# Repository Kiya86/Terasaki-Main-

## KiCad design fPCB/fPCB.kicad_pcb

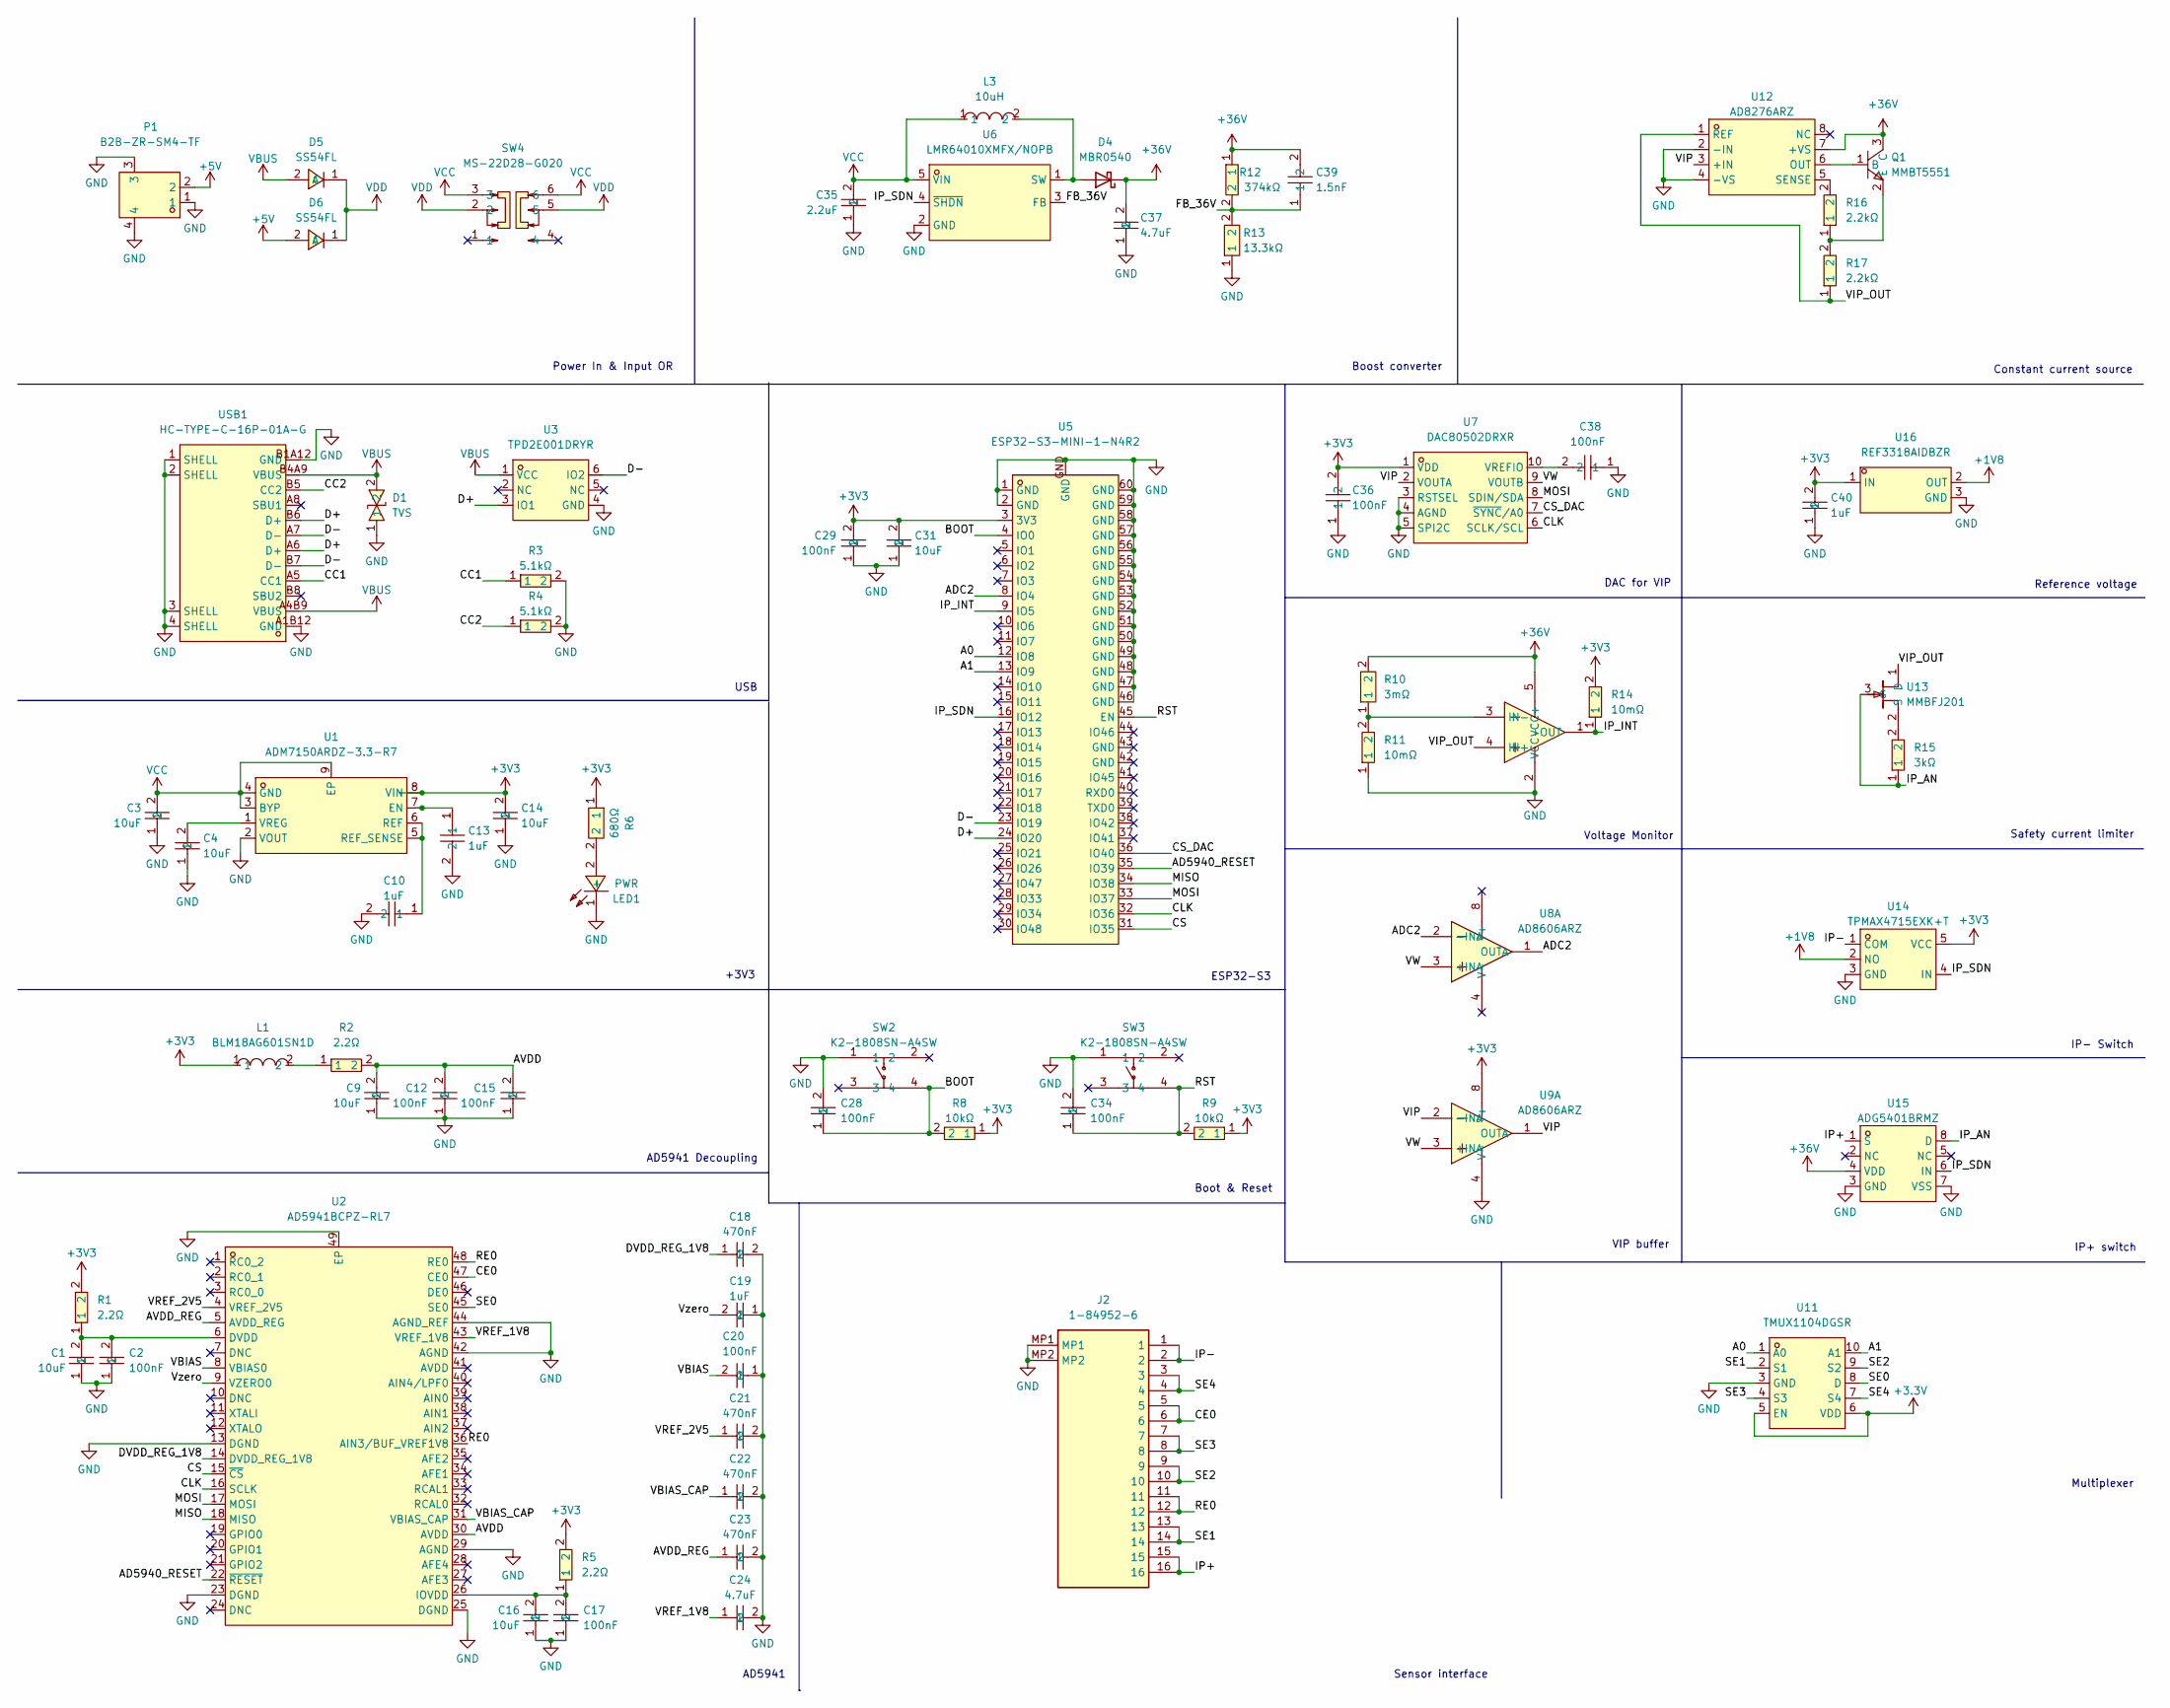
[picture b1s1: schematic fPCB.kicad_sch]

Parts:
C1, C9, C16, C31: 10uF; C0805; MPN CL21A106KOQNNNE; LCSC Part C1713
C2, C12, C15, C17, C20, C28, C29, C34: 100nF; C0603; MPN GRM188R71C104KA01D; LCSC Part C45000
C3, C4, C14: 10uF; C0805; MPN CL21B106KPQNNNE; LCSC Part C32635
C10, C13: 1uF; C0603; MPN CL10B105KP8NNNC; LCSC Part C95843
C18, C21, C22, C23: 470nF; C0402; MPN CC0402KRX5R6BB474; LCSC Part C106255
C19: 1uF; C0603; MPN CL10A105KO8NNNC; LCSC Part C1592
C24, C37: 4.7uF; C0603; MPN CL10A475KP8NNNC; LCSC Part C1705
C35: 2.2uF; C0603; MPN CL10A225KO8NNNC; LCSC Part C23630
C36, C38: 100nF; C0603; MPN GRM188R71H104KA93D; LCSC Part C77055
C39: 1.5nF; C0402; MPN GRM1555C1H152JA01D; LCSC Part C668348
C40: 1uF; C0402; MPN CL05A105KP5NNNC; LCSC Part C14445
D1: TVS; SOD-523_L1.2-W0.8-LS1.6-BI; MPN LESD5D5.0CT1G; LCSC Part C383211
D4: MBR0540; D_SOD-123
D5, D6: SS54FL; SMAF_L3.5-W2.6-LS4.7-RD; MPN SS54FL; LCSC Part C115939
J2: 1-84952-6; 1849526; Mouser Part Number 571-1-84952-6
L1: BLM18AG601SN1D; L0603; MPN BLM18AG601SN1D; LCSC Part C19330
L3: 10uH; L0603; MPN MLZ1608M100WT000; LCSC Part C76798
LED1: PWR; LED0805-RD; MPN NCD0805R1; LCSC Part C84256
P1: B2B-ZR-SM4-TF; CONN-SMD_B2B-ZR-SM4-TF-LF-SN; MPN B2B-ZR-SM4-TF(LF)(SN); LCSC Part C265284
Q1: MMBT5551; SOT-23-3_L2.9-W1.3-P1.90-LS2.4-BR; MPN MMBT5551; LCSC Part C916370
R1, R2, R5: 2.2Ω; R0402; MPN RC0402FR-072R2L; LCSC Part C327251
R3, R4: 5.1kΩ; R0402; MPN 0402WGF5101TCE; LCSC Part C25905
R6: 680Ω; R0402; MPN ERJ2RKF6800X; LCSC Part C413078
R8, R9: 10kΩ; R0603; MPN 0603WAJ0103T5E; LCSC Part C15401
R10: 3mΩ; R0603; MPN FRC0603J305 TS; LCSC Part C2907163
R11, R14: 10mΩ; R0603; MPN RC0603FR-0710ML; LCSC Part C114606
R12: 374kΩ; R0402; MPN 0402WGF3743TCE; LCSC Part C25781
R13: 13.3kΩ; R0402; MPN FRC0402F1332TS; LCSC Part C2974007
R15: 3kΩ; R0402; MPN RC0402FR-073KL; LCSC Part C137987
R16, R17: 2.2kΩ; R0603; MPN RC0603FR-072K2L; LCSC Part C114662
SW2, SW3: K2-1808SN-A4SW; KEY-SMD_4P-L4.2-W3.2-P2.20-LS5.1-TL; MPN K2-1808SN-A4SW-01; LCSC Part C92589
SW4: MS-22D28-G020; SW-SMD_MS-22D28-G020; MPN MS-22D28-G020; LCSC Part C963205
U1: ADM7150ARDZ-3.3-R7; SOIC-8_L4.9-W3.9-P1.27-LS6.0-BL-EP3.1; MPN ADM7150ARDZ-3.3-R7; LCSC Part C658444
U2: AD5941BCPZ-RL7; LFCSP-48_L7.0-W7.0-P0.50-BL-EP5.1; MPN AD5941BCPZ-RL7; LCSC Part C650309
U3: TPD2E001DRYR; SON-6_L1.5-W1.0-P0.50-BL; MPN TPD2E001DRYR; LCSC Part C379992
U5: ESP32-S3-MINI-1-N4R2; BULETM-SMD_ESP32-S3-MINI-1-N8; MPN ESP32-S3-MINI-1-N4R2; LCSC Part C3013941
U6: LMR64010XMFX/NOPB; SOT-23-5_L3.0-W1.7-P0.95-LS2.8-BR; MPN LMR64010XMFX/NOPB; LCSC Part C165138
U7: DAC80502DRXR; WSON-10_L2.5-W2.5-W0.50-BL; MPN DAC80502DRXR; LCSC Part C1880990
U8, U9: AD8606ARZ; SOIC-8_L4.9-W3.9-P1.27-LS6.0-BL; MPN AD8606ARZ; LCSC Part C578773
U10: TS391ILT; SOT-23-5_L3.0-W1.7-P0.95-LS2.8-BR; MPN TS391ILT; LCSC Part C71896
U11: TMUX1104DGSR; VSSOP-10_L3.0-W3.0-P0.50-LS4.9-BL; MPN TMUX1104DGSR; LCSC Part C2879206
U12: AD8276ARZ; SOIC-8_L4.9-W3.9-P1.27-LS6.0-BL; MPN AD8276ARZ; LCSC Part C652621
U13: MMBFJ201; SOT-23-3_L2.9-W1.3-P1.90-LS2.4-BR; MPN MMBFJ201; LCSC Part C891687
U14: TPMAX4715EXK+T; SOT-353_L2.2-W1.4-P0.65-LS2.4-BR; MPN TPMAX4715EXK+T; LCSC Part C46472308
U15: ADG5401BRMZ; MSOP-8_L3.0-W3.0-P0.65-LS4.9-BL; MPN ADG5401BRMZ; LCSC Part C657485
U16: REF3318AIDBZR; SOT-23-3_L3.0-W1.7-P0.95-LS2.9-BR; MPN REF3318AIDBZR; LCSC Part C115877
USB1: HC-TYPE-C-16P-01A-G; USB-C-SMD_G-SWITCH_GT-USB-7010EN; MPN HC-TYPE-C-16P-01A-G; LCSC Part C2997435

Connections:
+1V8: U14.2 (NO), U16.2 (OUT)
+3.3V: U11.5 (EN), U11.6 (VDD)
+3V3: C14.2, C29.2, C31.2, C36.2, C40.2, L1.1, R1.2, R5.2, R6.1, R8.1, R9.1, R14.2, U1.8 (VIN), U5.3 (3V3), U7.1 (VDD), U9.8 (V+), U14.5 (VCC), U16.1 (IN)
+5V: D6.2 (A), P1.2
+36V: C37.2, C39.2, D4.1 (K), Q1.3 (C), R10.2, R12.1, U10.5 (VCC+), U12.7 (+VS), U15.4 (VDD)
/A0: U5.12 (IO8), U11.1 (A0)
/A1: U5.13 (IO9), U11.10 (A1)
/AD5940_RESET: U2.22 (~RESET), U5.35 (IO39)
/ADC2: U5.8 (IO4), U8.1 (OUTA), U8.2 (-INA)
/AVDD: C9.2, C12.2, C15.2, R2.2, U2.30 (AVDD)
/AVDD_REG: C23.1, U2.5 (AVDD_REG)
/BOOT: C28.1, R8.2, SW2.4, U5.4 (IO0)
/CC1: R3.1, USB1.A5 (CC1)
/CC2: R4.1, USB1.B5 (CC2)
/CE0: J2.5, J2.6, U2.47 (CE0)
/CLK: U2.16 (SCLK), U5.32 (IO36), U7.6 (SCLK/SCL)
/CS: U2.15 (~CS), U5.31 (IO35)
/CS_DAC: U5.36 (IO40), U7.7 (~SYNC/A0)
/D+: U3.3 (IO1), U5.24 (IO20), USB1.A6 (D+), USB1.B6 (D+)
/D-: U3.6 (IO2), U5.23 (IO19), USB1.A7 (D-), USB1.B7 (D-)
/DVDD_REG_1V8: C18.1, U2.14 (DVDD_REG_1V8)
/FB_36V: C39.1, R12.2, R13.2, U6.3 (FB)
/IP+: J2.15, J2.16, U15.1 (S)
/IP-: J2.1, J2.2, U14.1 (COM)
/IP_AN: R15.1, U13.3 (G), U15.8 (D)
/IP_INT: R14.1, U5.9 (IO5), U10.1 (OUT)
/IP_SDN: U5.16 (IO12), U6.4 (~SHDN), U14.4 (IN), U15.6 (IN)
/MISO: U2.18 (MISO), U5.34 (IO38)
/MOSI: U2.17 (MOSI), U5.33 (IO37), U7.8 (SDIN/SDA)
/RE0: J2.11, J2.12, U2.36 (AIN3/BUF_VREF1V8), U2.48 (RE0)
/RST: C34.1, R9.2, SW3.4, U5.45 (EN)
/SE0: U2.45 (SE0), U11.8 (D)
/SE1: J2.13, J2.14, U11.2 (S1)
/SE2: J2.9, J2.10, U11.9 (S2)
/SE3: J2.7, J2.8, U11.4 (S3)
/SE4: J2.3, J2.4, U11.7 (S4)
/VBIAS: C20.2, U2.8 (VBIAS0)
/VBIAS_CAP: C22.1, U2.31 (VBIAS_CAP)
/VIP: U7.2 (VOUTA), U9.1 (OUTA), U9.2 (-INA), U12.3 (+IN)
/VIP_OUT: R17.1, U10.4 (IN+), U12.1 (REF), U13.1 (D)
/VREF_1V8: C24.1, U2.43 (VREF_1V8)
/VREF_2V5: C21.1, U2.4 (VREF_2V5)
/VW: U7.9 (VOUTB), U8.3 (+INA), U9.3 (+INA)
/Vzero: C19.2, U2.9 (VZERO0)
GND: C1.1, C2.1, C3.1, C4.1, C9.1, C10.2, C12.1, C13.2, C14.1, C15.1, C16.1, C17.1, C18.2, C19.1, C20.1, C21.2, C22.2, C23.2, C24.2, C28.2, C29.1, C31.1, C34.2, C35.1, C36.1, C37.1, C38.1, C40.1, D1.1, J2.MP1, J2.MP2, LED1.1 (-), P1.1, P1.3, P1.4, R3.2, R4.2, R11.1, R13.1, SW2.1, SW3.1, U1.2 (VOUT), U2.13 (DGND), U2.23 (DGND), U2.25 (DGND), U2.29 (AGND), U2.42 (AGND), U2.44 (AGND_REF), U2.49 (EP), U3.4 (GND), U5.1 (GND), U5.2 (GND), U5.46 (GND), U5.47 (GND), U5.48 (GND), U5.49 (GND), U5.50 (GND), U5.51 (GND), U5.52 (GND), U5.53 (GND), U5.54 (GND), U5.55 (GND), U5.56 (GND), U5.57 (GND), U5.58 (GND), U5.59 (GND), U5.60 (GND), U5.GND, U6.2 (GND), U7.3 (RSTSEL), U7.4 (AGND), U7.5 (SPI2C), U9.4 (V-), U10.2 (VCC-), U11.3 (GND), U12.2 (-IN), U12.4 (-VS), U14.3 (GND), U15.3 (GND), U15.7 (VSS), U16.3 (GND), USB1.1 (SHELL), USB1.2 (SHELL), USB1.3 (SHELL), USB1.4 (SHELL), USB1.A1B12 (GND), USB1.B1A12 (GND)
unnamed: D4.2 (A), L3.2, U6.1 (SW)
unnamed: L1.2, R2.1
unnamed: LED1.2 (+), R6.2
unnamed: Q1.1 (B), U12.6 (OUT)
unnamed: Q1.2 (E), R16.1, R17.2
unnamed: C13.1, U1.7 (EN)
unnamed: C10.1, U1.5 (REF_SENSE), U1.6 (REF)
unnamed: C4.2, U1.1 (VREG)
unnamed: C1.2, C2.2, R1.1, U2.6 (DVDD)
unnamed: C16.2, C17.2, R5.1, U2.26 (IOVDD)
unnamed: C38.2, U7.10 (VREFIO)
unnamed: R10.1, R11.2, U10.3 (IN-)
unnamed: R16.2, U12.5 (SENSE)
unnamed: R15.2, U13.2 (S)
VBUS: D1.2, D5.2 (A), U3.1 (VCC), USB1.A4B9 (VBUS), USB1.B4A9 (VBUS)
VCC: C3.2, C35.2, L3.1, SW4.3, SW4.6, U1.3 (BYP), U1.4 (GND), U1.9 (EP), U6.5 (VIN)
VDD: D5.1 (C), D6.1 (C), SW4.2, SW4.5

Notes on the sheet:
USB
Reference voltage
Voltage Monitor
AD5941 Decoupling
ESP32-S3
AD5941
Constant current source
+3V3
IP- Switch
Power In & Input OR
IP+ switch
Boot & Reset
DAC for VIP
Sensor interface
Safety current limiter
Multiplexer
VIP buffer
Boost converter

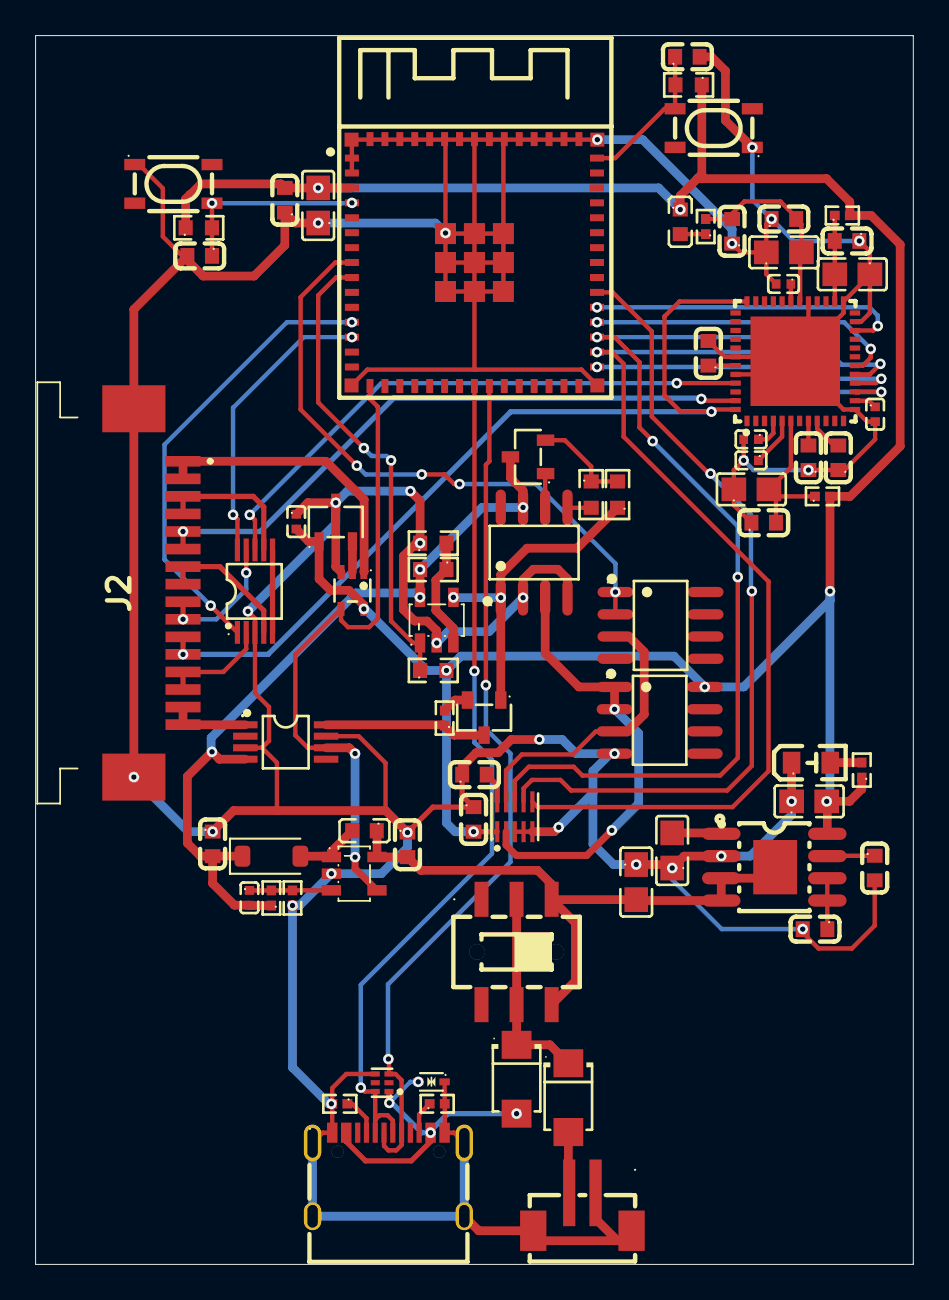
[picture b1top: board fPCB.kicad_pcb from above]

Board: 2 copper layers, 50.0 x 70.0 mm, 74 parts (0 on the bottom side), 62 nets.

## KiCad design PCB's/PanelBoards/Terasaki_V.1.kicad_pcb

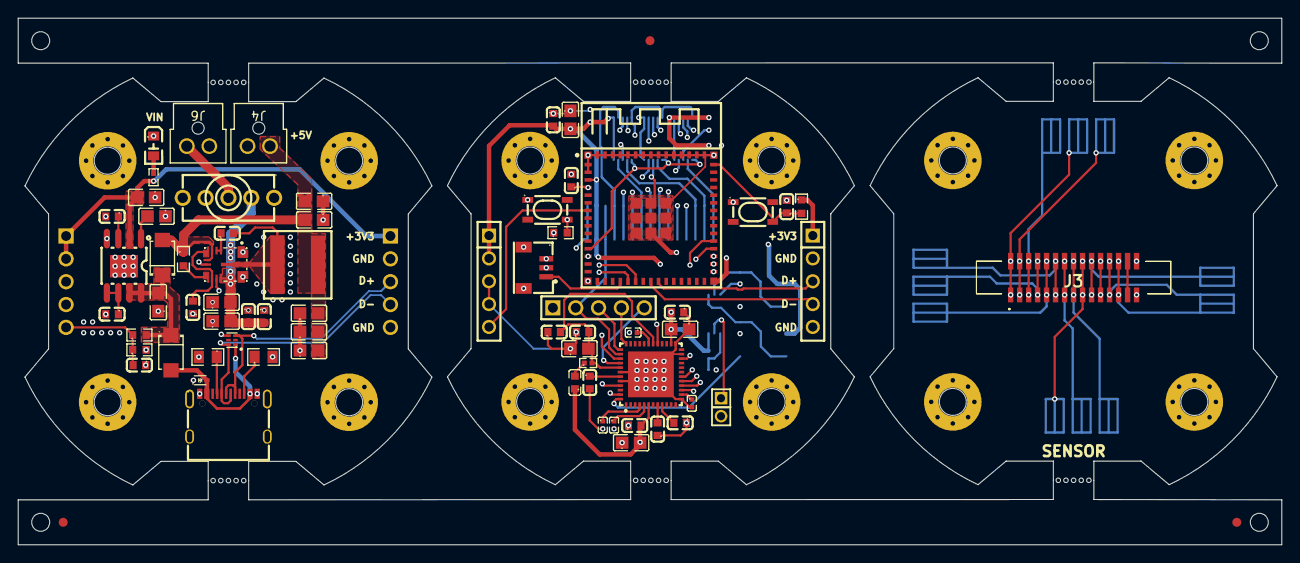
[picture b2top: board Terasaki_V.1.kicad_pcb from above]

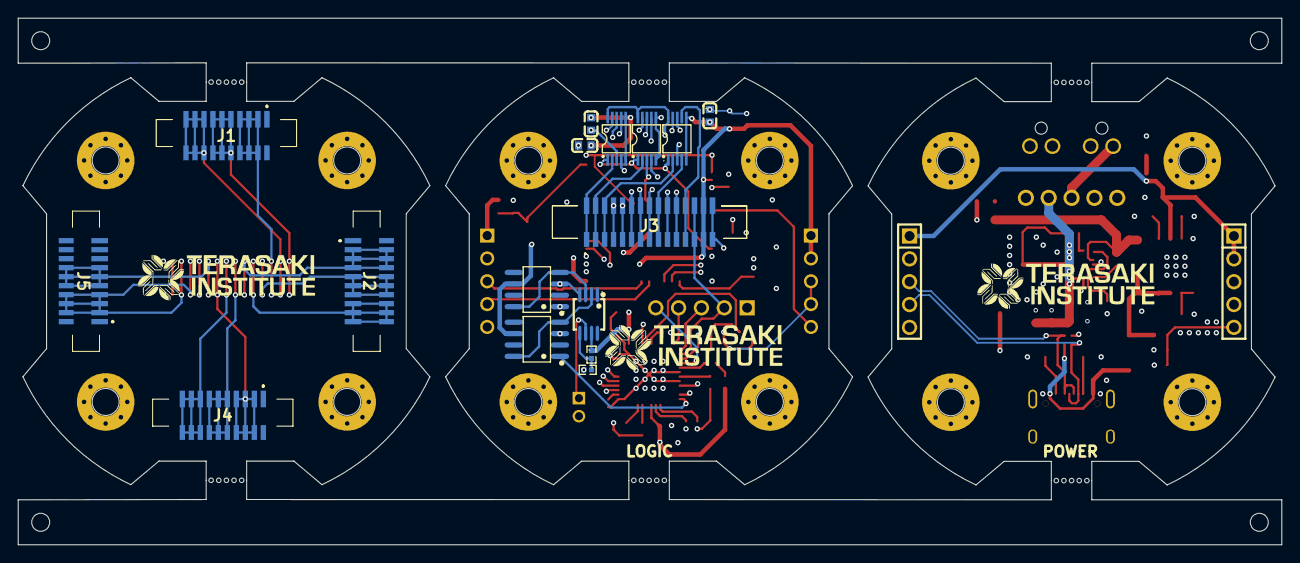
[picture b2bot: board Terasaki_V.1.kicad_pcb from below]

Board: 4 copper layers, 140.5 x 58.5 mm, 85 parts (18 on the bottom side), 65 nets.

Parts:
C1, C2, C3, C12, C16, C21, C27, C28, C34, C35, C36#2, C37#2, C38: 100nF; C0603
C5, C10, C37, C39: 1uF; C0603
C6, C11, C17, C18, C20, C22, C24, C26, C36: 10uF; C0805
C9, C25: 470nF; C0603
C13, C14, C15, C19, C23: 22uF; C0805
C29: 4.7uF; C0603
C30, C31, C32, C33: 470nF; C0402
D1: TVS; SOD-523_L1.2-W0.8-LS1.6-BI
D2, D3: SS54FL; SMAF_L3.5-W2.6-LS4.7-RD
H1: MTP220-1102S1; HDR-TH_2P-P2.00-V-M
H2, H3#2: A2541WV-5P; HDR-TH_5P-P2.54-V-M
H3, H4: Header-Female; HDR-TH_5P-P2.54-V-F
H5: Header; HDR-TH_5P-P2.54-H-M-W7.7-P
J1, J2, J4#2, J5: 1-1734248-0; 117342480
J3, J3#2: 52610-1572; 526101572
J4, J6: 1053091202; CONN_SD-105309-100_02_MOL
L1: 2.7uH; IND-SMD_L7.5-W7.5_XAL7030
L2: BLM18AG601SN1D; L0603
LED1: FC-2012HRK-620D; LED0805-RD
R1, R2, R9: 10kΩ; R0603
R3, R4: 5.5kΩ; R0805
R6, R10: 100kΩ; R0603
R7: 2.2Ω; R0402
R8: 680Ω; R0402
R12, R13: 100kΩ; R0402
SW1: 2MS1T2B2VS2QES; SW-TH_2MS1T2B2VS2QES
SW1#2, SW2: K2-1808SN-A4SW; KEY-SMD_4P-L4.2-W3.2-P2.20-LS5.1-TL
U1: ESP32-S3-MINI-1-N4R2; BULETM-SMD_ESP32-S3-MINI-1-N8
U2: INA333AIDGKR; MSOP-8_L3.0-W3.0-P0.65-LS5.0-BL
U3: TPD2E001DRYR; SON-6_L1.5-W1.0-P0.50-BL
U3#2, U5#2, U9#2: TMUX1104DGSR; VSSOP-10_L3.0-W3.0-P0.50-LS4.9-BL
U4: AD5941BCPZ-RL7; LFCSP-48_L7.0-W7.0-P0.50-BL-EP5.1
U5: ADM7150ARDZ-3.3-R7; SOIC-8_L4.9-W3.9-P1.27-LS6.0-BL-EP3.1
U6: BM03B-SRSS-TB; CONN-SMD-3P-P1.00_BM03B-SRSS-TB-LF-SN
U9: LM61495Q5RPHRQ1_C3188409; VQFN-16_L4.5-W3.5-P0.50-TL_TI_RPH
U11, U14: LMP7721MA/NOPB; SOIC-8_L4.9-W3.9-P1.27-LS6.0-BL
USB1: HC-TYPE-C-16P-01A-G; USB-C-SMD_G-SWITCH_GT-USB-7010EN

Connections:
+3V3: C1.2, C6.2, C17.2, C20.2, C21.2, C22.2, C35.2, C36#2.2, C37#2.2, C38.2, H2.1, H2.2, H3.1, H3.2, H3#2.1, H4.1, J3.27, J3.28, J3#2.27, J3#2.28, L2.1, R1.1, R2.1, R8.1, R12.1, U1.3 (3V3), U2.7 (V+), U3#2.5 (EN), U3#2.6 (VDD), U4.6 (DVDD), U4.26 (IOVDD), U5.2 (VOUT), U5#2.5 (EN), U5#2.6 (VDD), U9#2.5 (EN), U9#2.6 (VDD), U11.6 (V+), U14.6 (V+)
+5V: C13.2, C14.2, C15.2, C19.2, C23.2, D3.2 (A), J4.1, L1.2, R6.1, U9.5 (BIAS), U9.7 (FB)
+BATT: C9.2, C11.2, C25.2, C26.2, SW1.1, U9.2 (VIN2), U9.13 (EN), U9.14 (VIN1)
/A0: U1.12 (IO8), U3#2.1 (A0), U5#2.1 (A0), U9#2.1 (A0)
/A1: U1.13 (IO9), U3#2.10 (A1), U5#2.10 (A1), U9#2.10 (A1)
/AD5940_RESET: U1.35 (IO39), U4.22 (~RESET)
/AIN0: H1.2, H5.1, U4.39 (AIN0)
/AIN1: H5.2, J3.23, J3.24, J3.25, J3.26, J3#2.25, J3#2.26, J5.3, J5.4, J5.5, J5.6, J5.7, J5.8, U4.38 (AIN1)
/AIN2: H5.3, U4.37 (AIN2)
/AIN3: H5.4, U4.36 (AIN3/BUF_VREF1V8)
/AIN4: H5.5, U4.40 (AIN4/LPF0)
/AVDD: C24.2, C27.2, C34.2, R7.2, U4.30 (AVDD), U4.41 (AVDD)
/AVDD_REG: C32.1, U4.5 (AVDD_REG)
/BOOT: C2.1, R1.2, SW1#2.4, U1.4 (IO0)
/CB: C12.1, U9.3 (RBOOT), U9.4 (CBOOT)
/CC1: R3.1, USB1.A5 (CC1)
/CC2: R4.1, USB1.B5 (CC2)
/CE0: U4.47 (CE0), U5#2.8 (D)
/CE1: J1.15, J1.16, J1.17, J1.18, J1.19, J1.20, J3.3, J3.4, J3#2.3, J3#2.4, U5#2.2 (S1)
/CE2: J2.15, J2.16, J2.17, J2.18, J2.19, J2.20, J3.9, J3.10, J3#2.9, J3#2.10, U5#2.9 (S2)
/CE3: J3.15, J3.16, J3#2.15, J3#2.16, J4#2.15, J4#2.16, J4#2.17, J4#2.18, J4#2.19, J4#2.20, U5#2.4 (S3)
/CE4: J3.21, J3.22, J3#2.21, J3#2.22, U5#2.7 (S4)
/CLK: U1.32 (IO36), U4.16 (SCLK)
/CS: U1.31 (IO35), U4.15 (~CS)
/D+: H3#2.3, H4.3, U1.24 (IO20), U3.3 (IO1), USB1.A6 (D+), USB1.B6 (D+)
/D-: H3#2.4, H4.4, U1.23 (IO19), U3.6 (IO2), USB1.A7 (D-), USB1.B7 (D-)
/DVDD_REG_1V8: C33.1, U4.14 (DVDD_REG_1V8)
/MISO: U1.34 (IO38), U4.18 (MISO)
/MOSI: U1.33 (IO37), U4.17 (MOSI)
/OCPoutput: H1.1, U2.6 (VOUT)
/Poten_RE: U2.2 (VIN-), U14.4 (VOUT), U14.8 (IN-)
/Poten_WE: U2.3 (VIN+), U11.4 (VOUT), U11.8 (IN-)
/RE0: U3#2.8 (D), U4.48 (RE0), U14.1 (IN+)
/RE1: J1.3, J1.4, J1.5, J1.6, J1.7, J1.8, J3.5, J3.6, J3#2.5, J3#2.6, U3#2.2 (S1)
/RE2: J2.3, J2.4, J2.5, J2.6, J2.7, J2.8, J3.11, J3.12, J3#2.11, J3#2.12, U3#2.9 (S2)
/RE3: J3.17, J3.18, J3#2.17, J3#2.18, J4#2.3, J4#2.4, J4#2.5, J4#2.6, J4#2.7, J4#2.8, U3#2.4 (S3)
/RE4: J3#2.23, J3#2.24, U3#2.7 (S4)
/RST: C3.1, R2.2, SW2.4, U1.45 (EN)
/RT: C5.2, U9.6 (VCC), U9.9 (RT), U9.11 (SPSP)
/SE0: U4.45 (SE0), U9#2.8 (D), U11.1 (IN+)
/SE1: J1.9, J1.10, J1.11, J1.12, J1.13, J1.14, J3.1, J3.2, J3#2.1, J3#2.2, U9#2.2 (S1)
/SE2: J2.9, J2.10, J2.11, J2.12, J2.13, J2.14, J3.7, J3.8, J3#2.7, J3#2.8, U9#2.9 (S2)
/SE3: J3.13, J3.14, J3#2.13, J3#2.14, J4#2.9, J4#2.10, J4#2.11, J4#2.12, J4#2.13, J4#2.14, U9#2.4 (S3)
/SE4: J3.19, J3.20, J3#2.19, J3#2.20, J5.9, J5.10, J5.11, J5.12, J5.13, J5.14, U9#2.7 (S4)
/Servo_1: U1.19 (IO15), U6.1
/Servo_2: U1.20 (IO16), U6.2
/Servo_3: U1.21 (IO17), U6.3
/VBIAS: C28.2, U4.8 (VBIAS0)
/VBIAS_CAP: C31.1, U4.31 (VBIAS_CAP)
/VREF_1V8: C29.1, U4.43 (VREF_1V8)
/VREF_2V5: C30.1, U4.4 (VREF_2V5)
/V_ADC: C16.2, H2.5, H3.5, R9.1, R10.1, U1.7 (IO3)
/Vzero: C10.2, U4.9 (VZERO0)
GND: C1.1, C2.2, C3.2, C5.1, C6.1, C9.1, C10.1, C11.1, C13.1, C14.1, C15.1, C16.1, C17.1, C18.1, C19.1, C20.1, C21.1, C22.1, C23.1, C24.1, C25.1, C26.1, C27.1, C28.1, C29.2, C30.2, C31.2, C32.2, C33.2, C34.1, C35.1, C36.1, C36#2.1, C37.2, C37#2.1, C38.1, C39.2, D1.1, H2.3, H2.4, H3.3, H3.4, H3#2.2, H3#2.5, H4.2, H4.5, J3.29, J3.30, J3#2.29, J3#2.30, J4.2, J6.1, LED1.1 (-), R3.2, R4.2, R9.2, R13.2, SW1#2.1, SW2.1, U1.1 (GND), U1.2 (GND), U1.46 (GND), U1.47 (GND), U1.48 (GND), U1.49 (GND), U1.50 (GND), U1.51 (GND), U1.52 (GND), U1.53 (GND), U1.54 (GND), U1.55 (GND), U1.56 (GND), U1.57 (GND), U1.58 (GND), U1.59 (GND), U1.60 (GND), U1.GND, U2.4 (V-), U3.4 (GND), U3#2.3 (GND), U4.13 (DGND), U4.23 (DGND), U4.25 (DGND), U4.29 (AGND), U4.42 (AGND), U4.44 (AGND_REF), U4.49 (EP), U5.4 (GND), U5.9 (EP), U5#2.3 (GND), U6.4, U6.5, U9.1 (PGND2), U9.8 (AGND), U9.12 (SYNC/MODE), U9.15 (PGND1), U9#2.3 (GND), U11.3 (V-), U14.3 (V-), USB1.1 (SHELL), USB1.2 (SHELL), USB1.3 (SHELL), USB1.4 (SHELL), USB1.A1B12 (GND), USB1.B1A12 (GND)
unnamed: J6.2, SW1.2
unnamed: L2.2, R7.1
unnamed: LED1.2 (+), R8.2
unnamed: R12.2, R13.1, U2.5 (REF)
unnamed: C37.1, U5.3 (BYP)
unnamed: C39.1, U5.5 (REF_SENSE), U5.6 (REF)
unnamed: C36.2, U5.1 (VREG)
unnamed: C12.2, L1.1, U9.16 (SW)
unnamed: R6.2, U9.10 (~RESET)
VBUS: D1.2, D2.2 (A), U3.1 (VCC), USB1.A4B9 (VBUS), USB1.B4A9 (VBUS)
VCC: C18.2, D2.1 (C), D3.1 (C), R10.2, U5.7 (EN), U5.8 (VIN)

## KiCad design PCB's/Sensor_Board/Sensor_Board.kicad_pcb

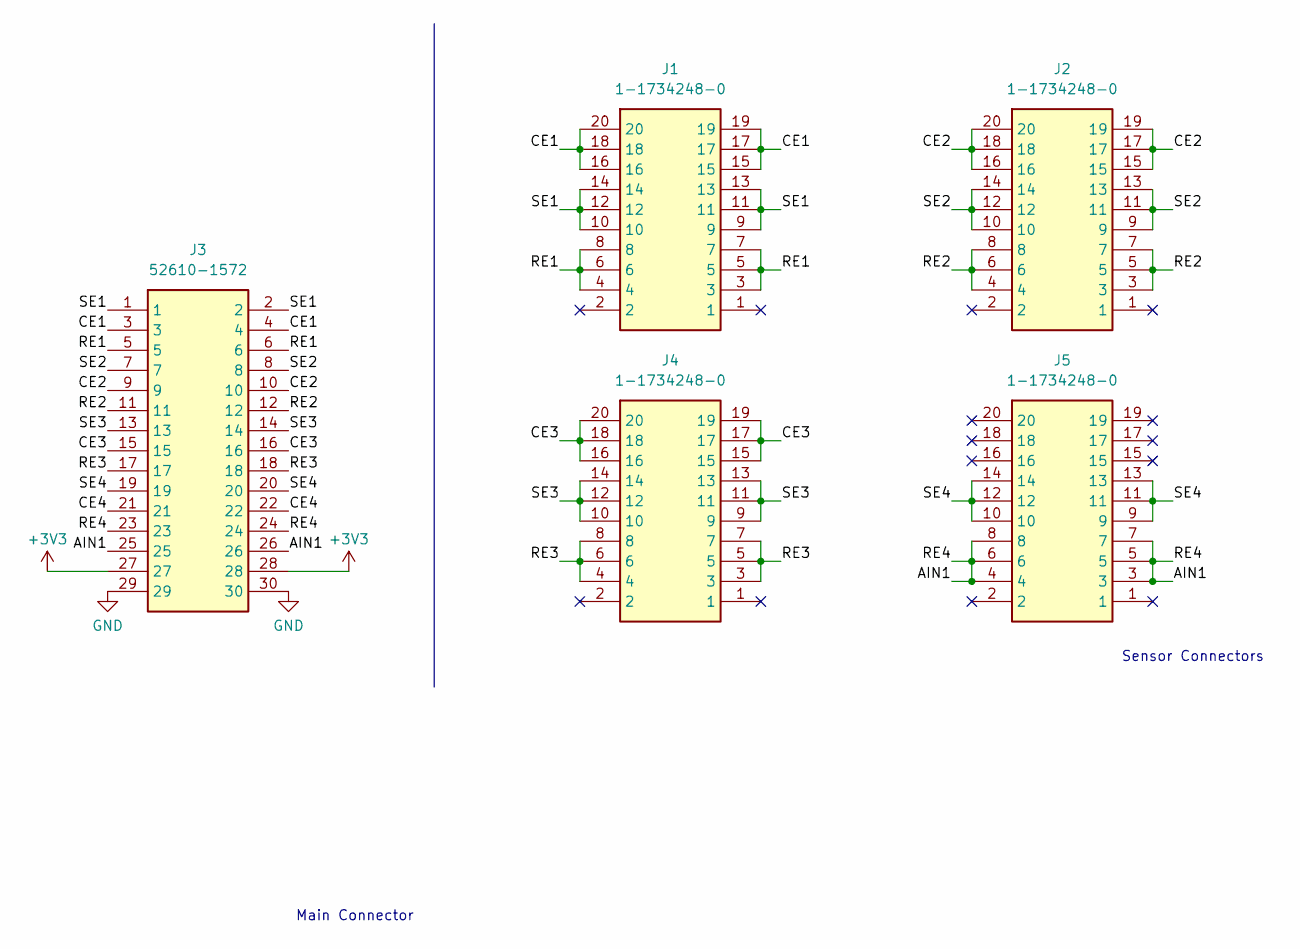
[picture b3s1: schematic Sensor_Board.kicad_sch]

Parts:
J1, J2, J4, J5: 1-1734248-0; 117342480; Mouser Part Number 571-1-1734248-0
J3: 52610-1572; 526101572; Mouser Part Number 538-52610-1572

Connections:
+3V3: J3.27, J3.28
/AIN1: J3.23, J3.24, J3.25, J3.26, J5.3, J5.4, J5.5, J5.6, J5.7, J5.8
/CE1: J1.15, J1.16, J1.17, J1.18, J1.19, J1.20, J3.3, J3.4
/CE2: J2.15, J2.16, J2.17, J2.18, J2.19, J2.20, J3.9, J3.10
/CE3: J3.15, J3.16, J4.15, J4.16, J4.17, J4.18, J4.19, J4.20
/CE4: J3.21, J3.22
/RE1: J1.3, J1.4, J1.5, J1.6, J1.7, J1.8, J3.5, J3.6
/RE2: J2.3, J2.4, J2.5, J2.6, J2.7, J2.8, J3.11, J3.12
/RE3: J3.17, J3.18, J4.3, J4.4, J4.5, J4.6, J4.7, J4.8
/SE1: J1.9, J1.10, J1.11, J1.12, J1.13, J1.14, J3.1, J3.2
/SE2: J2.9, J2.10, J2.11, J2.12, J2.13, J2.14, J3.7, J3.8
/SE3: J3.13, J3.14, J4.9, J4.10, J4.11, J4.12, J4.13, J4.14
/SE4: J3.19, J3.20, J5.9, J5.10, J5.11, J5.12, J5.13, J5.14
GND: J3.29, J3.30

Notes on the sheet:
Sensor Connectors
Main Connector

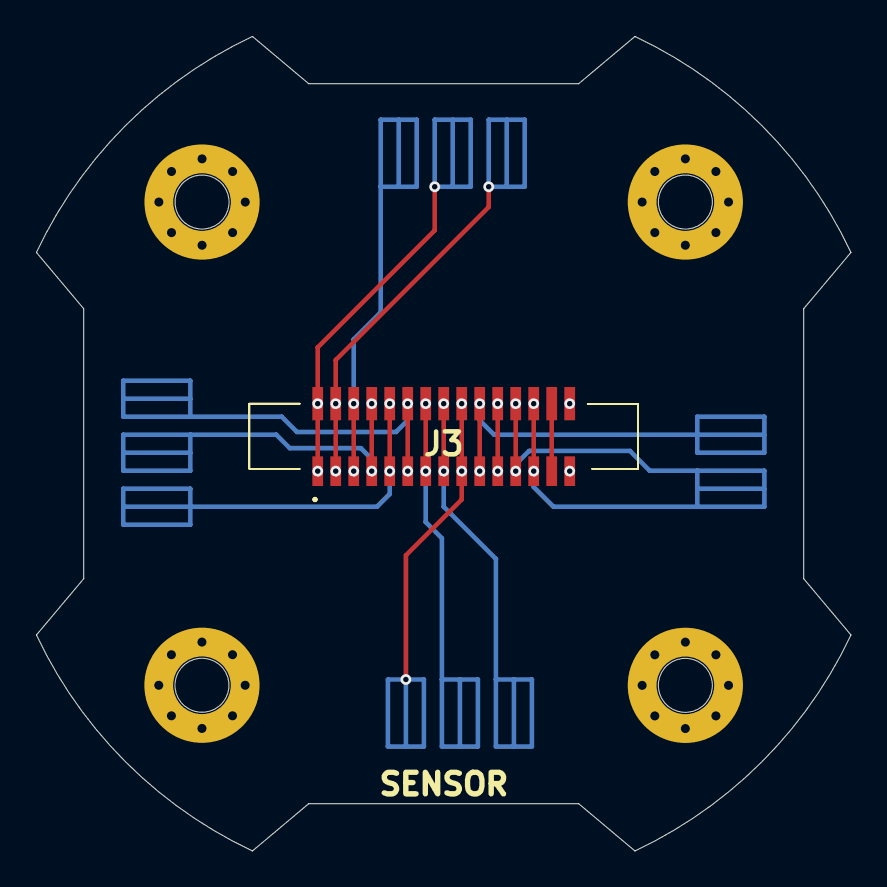
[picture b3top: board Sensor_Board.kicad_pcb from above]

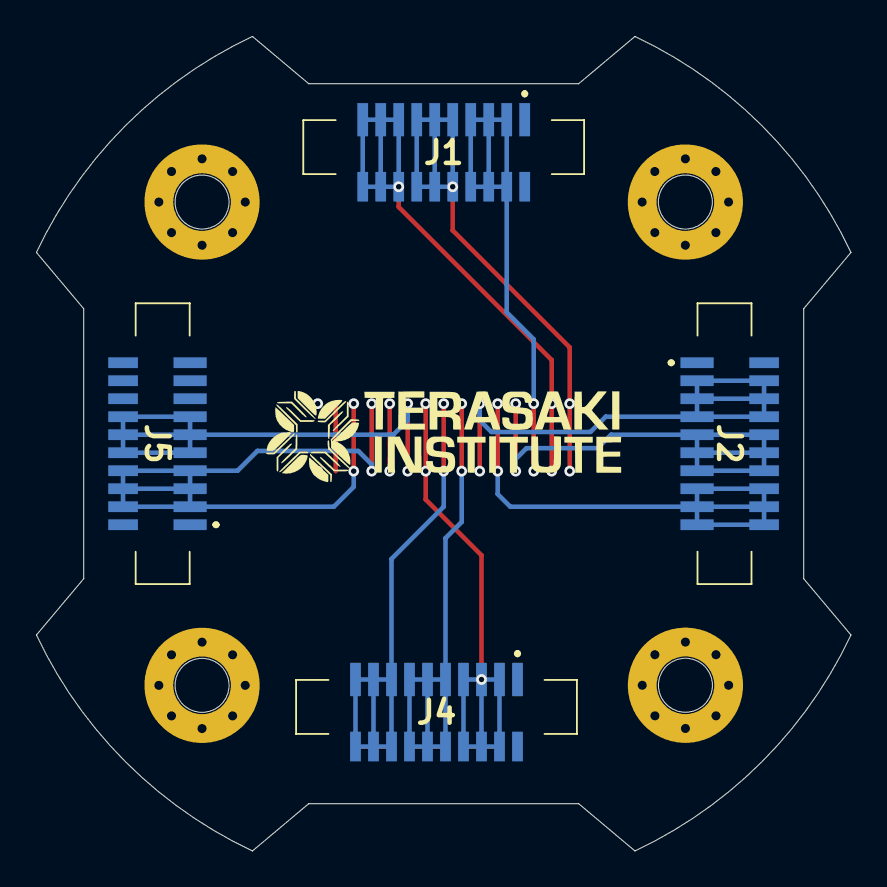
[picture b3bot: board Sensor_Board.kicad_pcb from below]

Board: 4 copper layers, 45.2 x 45.2 mm, 5 parts (4 on the bottom side), 14 nets.
